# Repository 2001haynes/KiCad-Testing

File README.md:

# KiCad-Testing
Testing KiCad-Git integration

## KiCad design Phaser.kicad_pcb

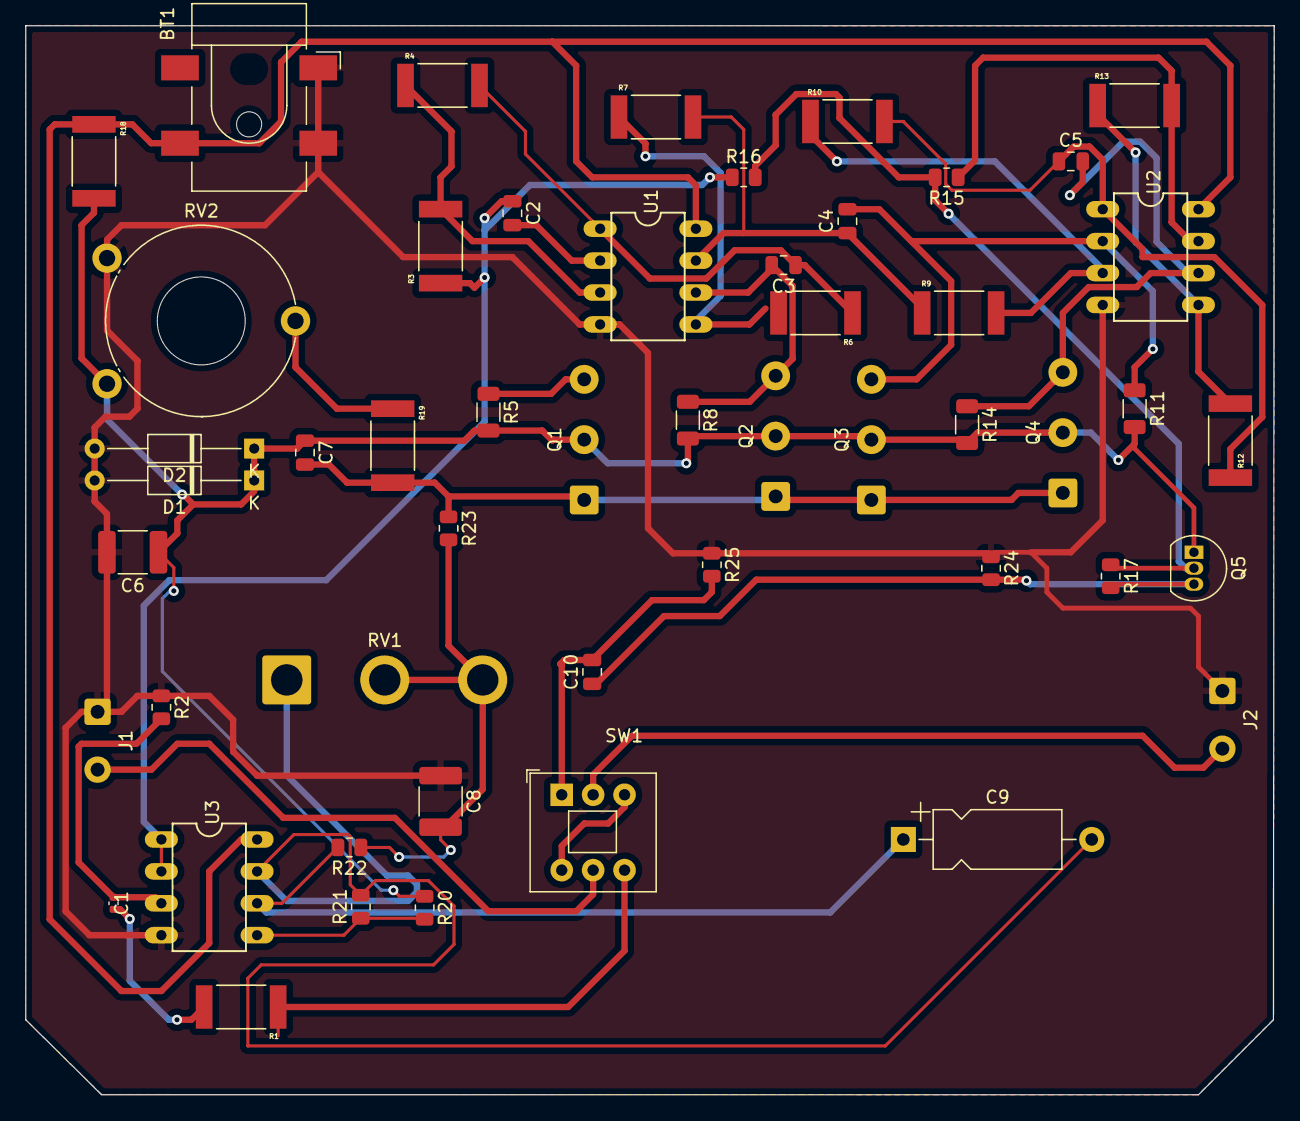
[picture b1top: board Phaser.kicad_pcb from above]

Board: 2 copper layers, 99.4 x 85.1 mm, 51 parts (0 on the bottom side), 31 nets.

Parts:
BT1: 9VDC; BarrelJack_CLIFF_FC681465S_SMT_Horizontal
C1: 0.01uF; C_0402_1005Metric
C2, C3, C4, C5, C7, C10: 47nF; C_0805_2012Metric
C6, C8: 15uF; C_1812_4532Metric
C9: 0.01F; CP_Axial_L10.0mm_D4.5mm_P15.00mm_Horizontal
D1: D; D_DO-35_SOD27_P12.70mm_Horizontal
D2: 5.1V; D_DO-35_SOD27_P12.70mm_Horizontal
J1, J2: Barrel_Jack; SolderWire-0.5sqmm_1x02_P4.6mm_D0.9mm_OD2.1mm
Q1, Q2, Q3, Q4: Q_NJFET_GDS; SolderWire-0.5sqmm_1x03_P4.8mm_D0.9mm_OD2.3mm
Q5: 2N3904; TO-92_Inline
R1: 10kOhm; RESC6332X70N
R2: 470kOhm; R_0805_2012Metric
R3, R4, R6, R7, R9, R10, R12, R13, R18: 10k; RESC6332X70N
R5, R8, R11, R14: 24k; R_1206_3216Metric
R15, R16, R17, R20, R22, R24, R25: 150k; R_0805_2012Metric
R19: 1Meg; RESC6332X70N
R21: 470k; R_0805_2012Metric
R23: 3.9Meg; R_0805_2012Metric
RV1: 470k; SolderWire-2sqmm_1x03_P7.8mm_D2mm_OD3.9mm
RV2: 250k; Potentiometer_Piher_PT-15-V15_Vertical_Hole
SW1: SW_DPDT_x2; SW_Push_2P2T_Toggle_CK_PVA2OAH5xxxxxxV2
U1, U2, U3: TL062; DIL08

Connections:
5.1Vref: C6.1, C7.1, D1.1 (K), D2.1 (K), Q1.2 (D), Q2.2 (D), Q3.2 (D), Q4.2 (D), Q5.1 (E), R5.2, R8.2, R11.2, R14.2, R18.2, R20.1, RV2.1
GND: BT1.1 (+), C6.2, C8.1, D1.2 (A), D2.2 (A), J1.1, J2.1, R2.1, R24.1, R25.1, RV2.3, U1.4 (V-), U2.4 (V-), U3.4 (V-)
unnamed: C1.1, R2.2, U3.3 (+)
unnamed: C1.2, R1.2
unnamed: C2.1, R3.1, R16.1, U3.1, U3.2 (-)
unnamed: C2.2, Q1.3 (S), R5.1, U1.2 (-)
unnamed: C3.1, R4.2, R6.1, U1.1
unnamed: C3.2, Q2.3 (S), R8.1, U1.6 (-)
unnamed: C4.1, R7.2, R9.1, U1.7
unnamed: C4.2, Q3.3 (S), R11.1, U2.2 (-)
unnamed: C5.1, R10.2, R12.1, U2.1
unnamed: C5.2, Q4.3 (S), R14.1, U2.6 (-)
unnamed: C8.2, R22.1, R23.2, RV1.2, RV1.3
unnamed: C9.1, R22.2, U3.6 (-)
unnamed: C9.2, R21.2, RV1.1, U3.7
unnamed: C10.1, Q5.3 (C), R17.2, R24.2
unnamed: C10.2, R25.2, SW1.1 (A)
unnamed: J1.2, SW1.5 (B)
unnamed: J2.2, SW1.2 (B)
unnamed: Q5.2 (B), R15.2, R16.2, R17.1
unnamed: R1.1, SW1.6 (C)
unnamed: R3.2, R4.1, U1.3 (+)
unnamed: R6.2, R7.1, U1.5 (+)
unnamed: R9.2, R10.1, U2.3 (+)
unnamed: R12.2, R13.1, U2.5 (+)
unnamed: R13.2, R15.1, U2.7
unnamed: R19.1, RV2.2
unnamed: R20.2, R21.1, U3.5 (+)
unnamed: SW1.3 (C), SW1.4 (A)
unnamed: BT1.2 (-), R18.1, U1.8 (V+), U2.8 (V+), U3.8 (V+)
Vbias: C7.2, Q1.1 (G), Q2.1 (G), Q3.1 (G), Q4.1 (G), R19.2, R23.1

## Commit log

2024-01-10 Base PCB files upload
2024-01-10 Testing PCB upload
2024-01-10 Phaser Edit 1
